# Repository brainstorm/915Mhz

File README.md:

# 915Mhz RF filter breakout boards

This is an experiment with a 915Mhz LoRa module and SAW filters as a substitute for discrete components. The original *raison d'être* of this repository is my personal outrage after seeing the following **$100 evaluation board** for the [PE4259](https://www.psemi.com/pdf/datasheets/pe4259ds.pdf):

And indeed, [AppliedCarbon from OSHPark also thought so and designed a smaller PCB](https://oshpark.com/shared_projects/2MRloEFC).

Gold tracks and pads, many vias and proper RF engineering, sure, but $100 plus shipping? Let's see how the homemade way works in comparison? On the **`master`** branch of this repository, I'm putting together a board with the RF switch and the SAW filter (will be using a 915 Mhz [sf2098e "low insertion loss" SAW filter](https://wireless.murata.com/RFM/data/sf2098e.pdf), no frills design for now. I might put the vias in place if needed in the future and compare performance/loss and the accompanying [S parameters](https://en.wikipedia.org/wiki/Scattering_parameters).

But since the approach above might not be modular enough for my testing purposes (thanks Chris), I've forked that layout into two branches:

```bash
$ git branch -a
* master
  rf_switch_only
  saw_filter_only
```

Here's how each of those look like at the moment of writing this, let's play "spot the differences", shall we?:

Now, as with the [Instructables Carvey Board project](https://github.com/brainstorm/carvey_board), I've generated some G-Code (under the **homefab** subdirectory) with [FlatCam](http://flatcam.org/) to carve those board at home, wish me luck with the spectrum analyzers and followup testing!

Alternatively, there's a .zip under homefab, containing the ready-to-send gerbers to i.e Seed Studios or any other PCB manufacturer. Here's the latest iteration of the rf matching board on `master`:

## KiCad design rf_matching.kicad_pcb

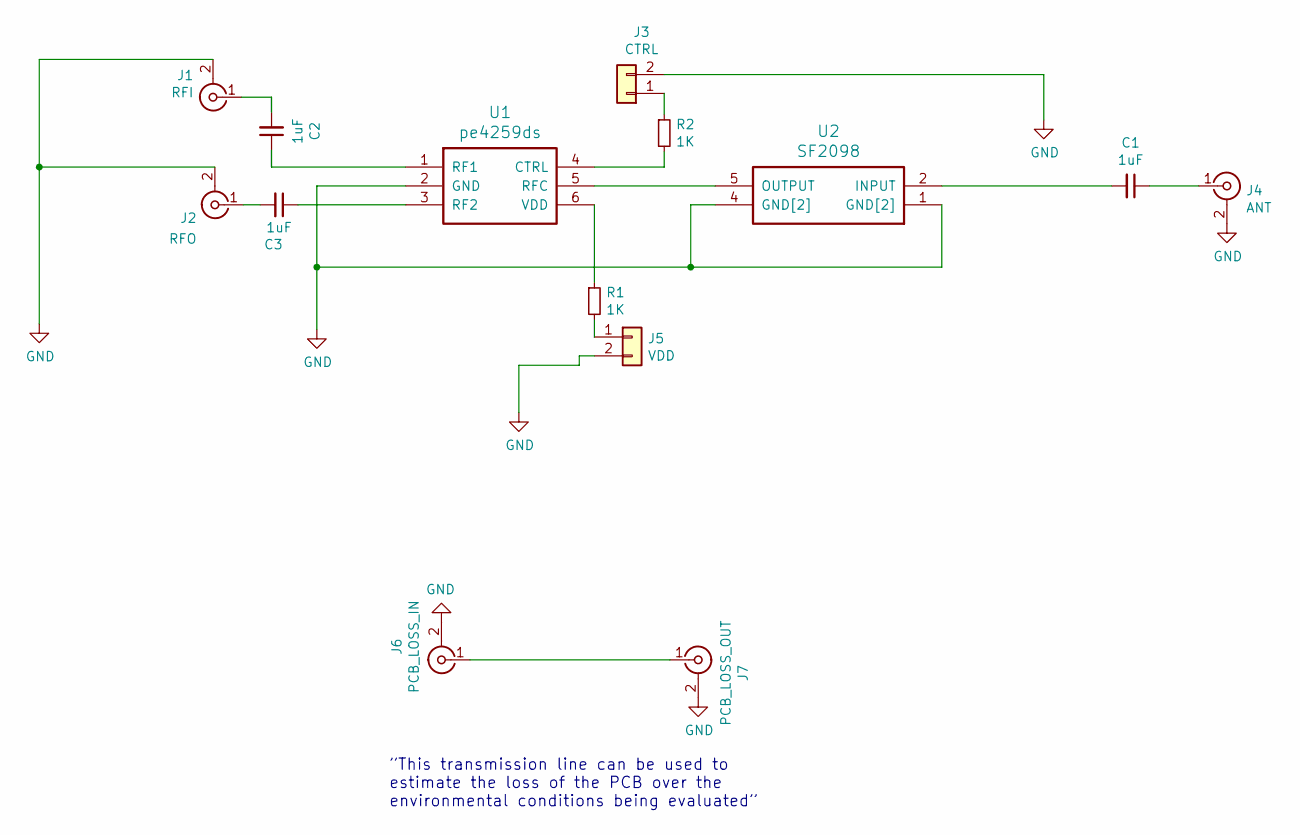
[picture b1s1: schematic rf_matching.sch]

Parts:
C1, C2, C3: 1uF; C_0603
J1: RFI; Molex_SMA_Jack_Edge_Mount
J2: RFO; Molex_SMA_Jack_Edge_Mount
J3: CTRL; Molex_KK-6410-02_02x2.54mm_Straight
J4: ANT; Molex_SMA_Jack_Edge_Mount
J5: VDD; Molex_KK-6410-02_02x2.54mm_Straight
J6: PCB_LOSS_IN; Molex_SMA_Jack_Edge_Mount
J7: PCB_LOSS_OUT; Molex_SMA_Jack_Edge_Mount
R1, R2: 1K; R_0603
U1: pe4259ds; SC70-6_Pitch-0.65_2.00x2.10x1.00mm
U2: SF2098; SON120P300X300X110-6N

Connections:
GND: J1.2 (Ext), J2.2 (Ext), J3.2, J4.2 (Ext), J5.2, J6.2 (Ext), J7.2 (Ext), U1.2 (GND), U2.1 (GND[2]), U2.3 (GND[2]), U2.4 (GND[2]), U2.6 (GND[2])
unnamed: C1.1, J4.1 (In)
unnamed: C1.2, U2.2 (INPUT)
unnamed: C2.1, U1.1 (RF1)
unnamed: C2.2, J1.1 (In)
unnamed: C3.1, U1.3 (RF2)
unnamed: C3.2, J2.1 (In)
unnamed: J3.1, R2.1
unnamed: J5.1, R1.2
unnamed: J6.1 (In), J7.1 (In)
unnamed: R1.1, U1.6 (VDD)
unnamed: R2.2, U1.4 (CTRL)
unnamed: U1.5 (RFC), U2.5 (OUTPUT)

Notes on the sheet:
”This transmission line can be used to estimate the loss of the PCB over the environmental conditions being evaluated”

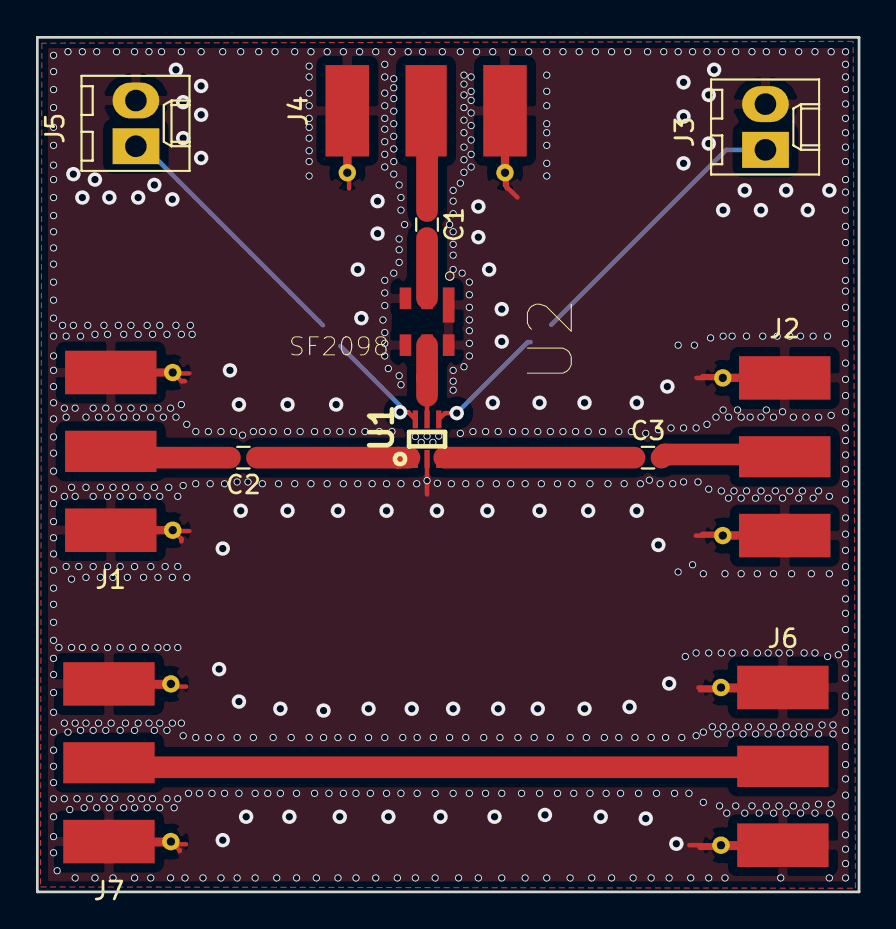
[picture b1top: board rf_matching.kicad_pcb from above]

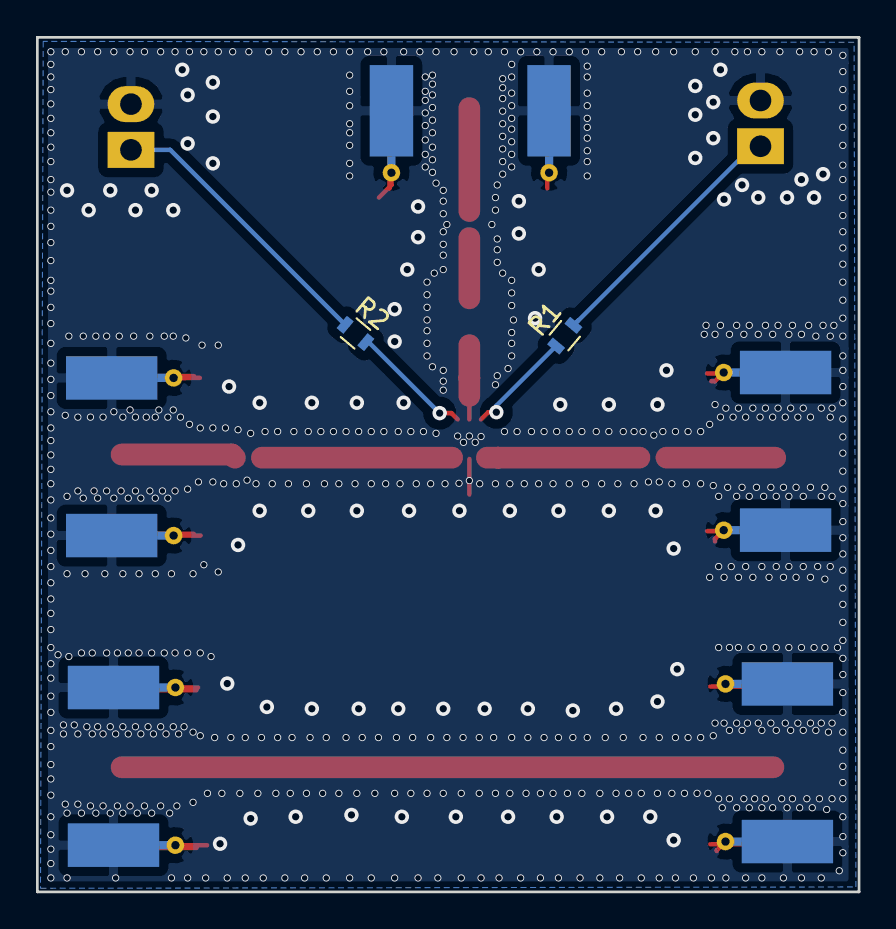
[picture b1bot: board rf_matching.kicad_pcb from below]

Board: 2 copper layers, 45.7 x 47.5 mm, 14 parts (2 on the bottom side), 13 nets.

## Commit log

2018-07-22 Initial RF switch and SAW filter layout
2018-07-22 Fixing ground plane dubiously through the connectors, sparing a link and going single layer... will it work/perform well?
2018-07-22 RF switch only branch
2018-07-22 Version with the board with just the saw filter, no vias yet
2018-07-22 Add gcode for saw filter only
2018-07-22 Add isolation routing and board cutout for rf_switch only branch
2018-07-22 Add gerbers and gcode for the combined rf switch and SAW filter board
2018-07-22 Add minimal README about the project and brief explanation on where to find the G-Code, branches for each experiment, etc...
2018-07-24 Update board isolation and cutout g-code so that it complies with Easel restrictions: https://inventables.desk.com/customer/portal/articles/2258567-easel-g-code-spec
2018-09-01 Add thicker bias, add PCB LOSS line
2018-09-04 Redesign, more similar to official evaluation board
2018-09-04 Add by-hand vias, silly semi-random placement
2018-09-04 Add current iteration image, boards sent to Seed Studios via promotion pricing: https://twitter.com/braincode/status/1036909730244034560
2019-01-04 I am not alone in this :)
